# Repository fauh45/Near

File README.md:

# Near

Near is a connected IoT project for couples, friends, and more. It's an exploration on how a simple device could connect people together.

## v1 (MOOD LIGHT)

Version 1 of the Near project is pretty simple, an interconnected small RGB LED mood light device that can trigger the other mood light.
The idea currently is to be simply put on a desk or places where people spend their day most of the time, thus they can receive a simple
notification through the light from other people in the interconnected network of the device.

An exploration of usage of this device could also lead for it to be able to be triggered from external event, or some kind of time-based
event that's important to one or all the device in the interconnected network of it. The concept stays simple, while each other might not
be there, the notification, or "nag" that they receive hopefully make them feel more together.

### Technicality

It's a super simple device. Consisting of ESP32-C3 Super Mini as the MCU, a button, 4 addressable RGB, and 2 capacitors. All of it are mounted on
a small (25 x 28mm) PCB board. All of it mounted on a SMD mounting.

### Timeline

- 27 November 2024, finalized the design, and start the PCB and parts order
- 1 March 2025, two device have been built, firmware nearing beta phase

## Credits

H❤️F Engineering, 2025.

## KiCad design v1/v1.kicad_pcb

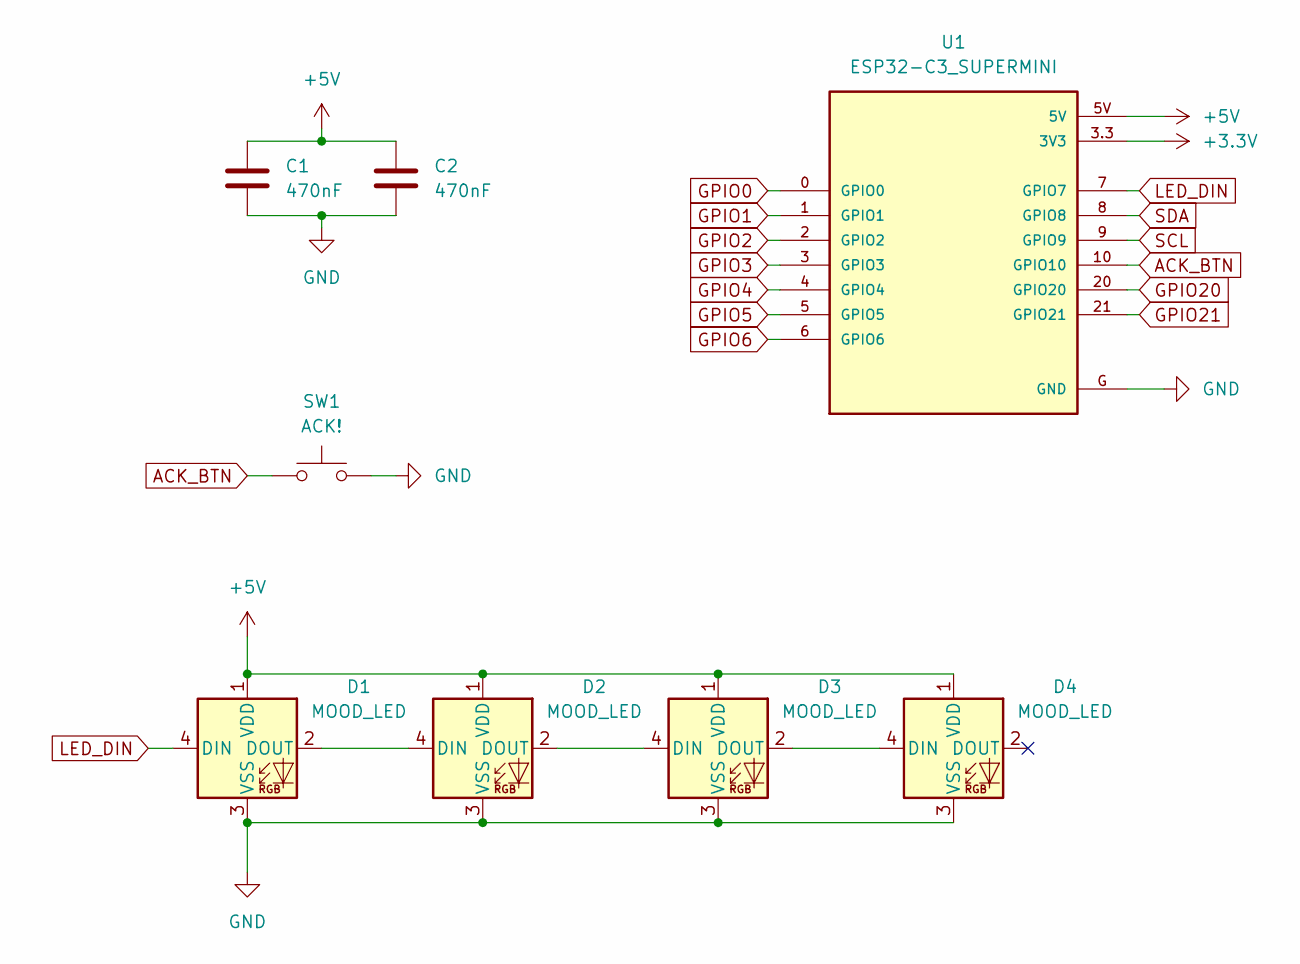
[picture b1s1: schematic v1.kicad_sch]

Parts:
C1, C2: 470nF; C_0805_2012Metric_Pad1.18x1.45mm_HandSolder
D1, D2, D3, D4: MOOD_LED; LED_WS2812B_PLCC4_5.0x5.0mm_P3.2mm
SW1: ACK!; SW_SPST_Omron_B3FS-100xP
U1: ESP32-C3_SUPERMINI; MODULE_ESP32-C3_SUPERMINI

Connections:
+3.3V: U1.3.3 (3V3)
+5V: C1.1, C2.1, D1.1 (VDD), D2.1 (VDD), D3.1 (VDD), D4.1 (VDD), U1.5V
ACK_BTN: SW1.1, U1.10 (GPIO10)
GND: C1.2, C2.2, D1.3 (VSS), D2.3 (VSS), D3.3 (VSS), D4.3 (VSS), SW1.2, U1.G (GND)
GPIO0: U1.0 (GPIO0)
GPIO1: U1.1 (GPIO1)
GPIO2: U1.2 (GPIO2)
GPIO3: U1.3 (GPIO3)
GPIO4: U1.4 (GPIO4)
GPIO5: U1.5 (GPIO5)
GPIO6: U1.6 (GPIO6)
GPIO20: U1.20 (GPIO20)
GPIO21: U1.21 (GPIO21)
LED_DIN: D1.4 (DIN), U1.7 (GPIO7)
unnamed: D1.2 (DOUT), D2.4 (DIN)
unnamed: D2.2 (DOUT), D3.4 (DIN)
unnamed: D3.2 (DOUT), D4.4 (DIN)
SCL: U1.9 (GPIO9)
SDA: U1.8 (GPIO8)

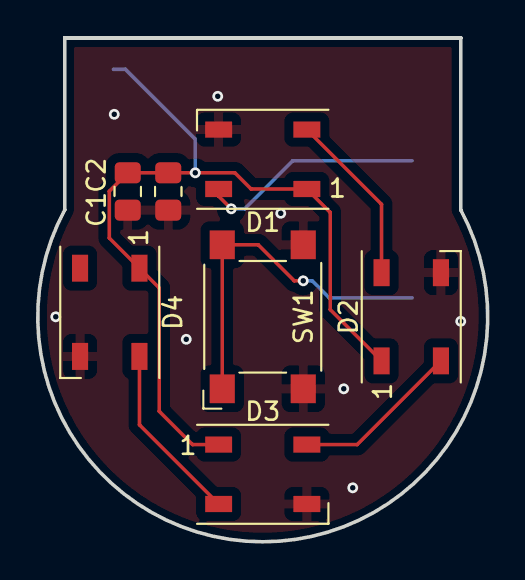
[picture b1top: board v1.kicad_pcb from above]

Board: 2 copper layers, 25.0 x 28.0 mm, 8 parts (1 on the bottom side), 7 nets.

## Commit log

2024-11-28 feat: v1 near
2024-11-28 chore: firmware ideas
2024-11-29 feat: initialize firmware with esp idf
2024-11-29 docs: add link to useful walkthrough
2024-11-30 chore: set the target to be ESP32-C3
2024-11-30 chore: add uuid converter
2024-11-30 feat: working bt le broadcast with service id
2024-11-30 feat: add characteristic struct to save each characteristic function
2024-11-30 docs: first step done!
2024-12-01 chore: remove BT5.0 features for now
2024-12-01 feat: working improv characteristics
2024-12-02 feat: working characteristic read
2024-12-02 feat: initialize the notify CCC descriptor for all characteristic
2024-12-02 feat: working NOTIFY enable?
2024-12-02 docs: service data might not be correct
2024-12-14 feat: handle long write
2024-12-14 feat: add rpc handler
2024-12-14 feat: add notify on new error state
2024-12-14 feat: start wifi and networking stack
2024-12-14 fix: ssid and password not initialized
2024-12-14 fix: build not includes improv.c
2024-12-15 fix: nvs is too small for factory
2024-12-15 fix: without response packet not handled
2024-12-15 fix: string print, test state change
2025-02-11 feat: add wifi initialization
    also fix IMPROV_CAPABILITIES to bit 1 instead of 0
2025-02-11 feat: working wifi connection
2025-02-12 feat: working wifi connection from nvs
2025-02-13 chore: use defaults instead of sdkconfig for configurable builds
2025-02-13 chore: dynamic configuration for MQTT
2025-02-13 chore: move Kconfig to the right location
2025-03-01 feat: connect mqtt with valid SSL validation
2025-03-01 chore: update copyright year
2025-03-01 feat: update progress
2025-03-09 feat: initial ws2812b driver
2025-03-09 feat: handle provisioning and errors with leds
2025-03-09 feat: add configuration for colour sent
2025-03-09 feat: working mqtt messaging!
2025-03-09 chore: defaults to 80MHz
2025-03-09 docs: update documentations
2025-03-09 fix: somewhat fixed the rmt timing
2025-03-10 fix: better result somehow
2025-03-15 feat: add website for firmware update
2025-03-15 fix: move all js requirements to locally hosted
2025-03-15 fix: reduce status led even more
